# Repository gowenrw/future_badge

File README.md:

# future_badge

Future Badge Artifacts

This is a DEFCON Indie badge created for DC31.

This is where all the files for the Future Badge will be stored.

This includes code and art and cad and fab files.  All the things.

## File Structure

This is the file structure of this repository

* [/](/README.md) - YOU ARE HERE
* [/art/](./art/) - Artwork and other graphics created by this project
  * [/art/inspiration/](./art/inspiration/) - Art and graphics pulled from other sources used as inspiration for this project
  * [/art/fonts/](./art/fonts/) - Fonts used in art and graphics
* [/code/](./code/) - All project related Code / Firmware
* [/docs/](./docs/) - Documentation created by this project including web pages
* [/eda/](./eda/) - Electronic Design Automation files (i.e. KiCad)
  * [/eda/future_badge/](./eda/future_badge/) - KiCad 6.x project folder for the future_badge PCB
* [/reference_parts/](./reference_parts/) - Documentation pulled from other sources related to components
* [/README.md](/README.md) - This File
* [/LICENSE](/LICENSE) - Currently set to MIT

Note: the reference_parts directory is a link to a submodule repository.
To add it use the following cmd after cloning this:
```
git submodule add https://github.com/gowenrw/reference_parts reference_parts
```
This will make a link to the current commit of that repo.
To update it to a newer commit after its been added use this cmd:
```
git submodule update --init --recursive
```

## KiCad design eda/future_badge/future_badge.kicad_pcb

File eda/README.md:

# Electronic Design Automation

This is where all the Electronic Design Automation files for the PCB(s) will be stored.
The EDA used is KiCad 6.x unless otherwise specified.

## File Structure

This is the file structure of this repository

* [/](/README.md) - Home
* [/eda](/eda/) - YOU ARE HERE
  * /eda/<eda_project>/ - KiCad project folder for the named project PCB(s)
    * ./3d_models/ - This directory contains footprint 3d model files
    * ./gerber/ - This directory contains gerber formatted files for manufacturing
    * ./lib_fp/ - This directory contains footprint module directories
    * ./lib_sh/ - This directory contains schematic library files
    * ./snapshots/ - This directory contains prints of schematic / cad files and images of preview / final product

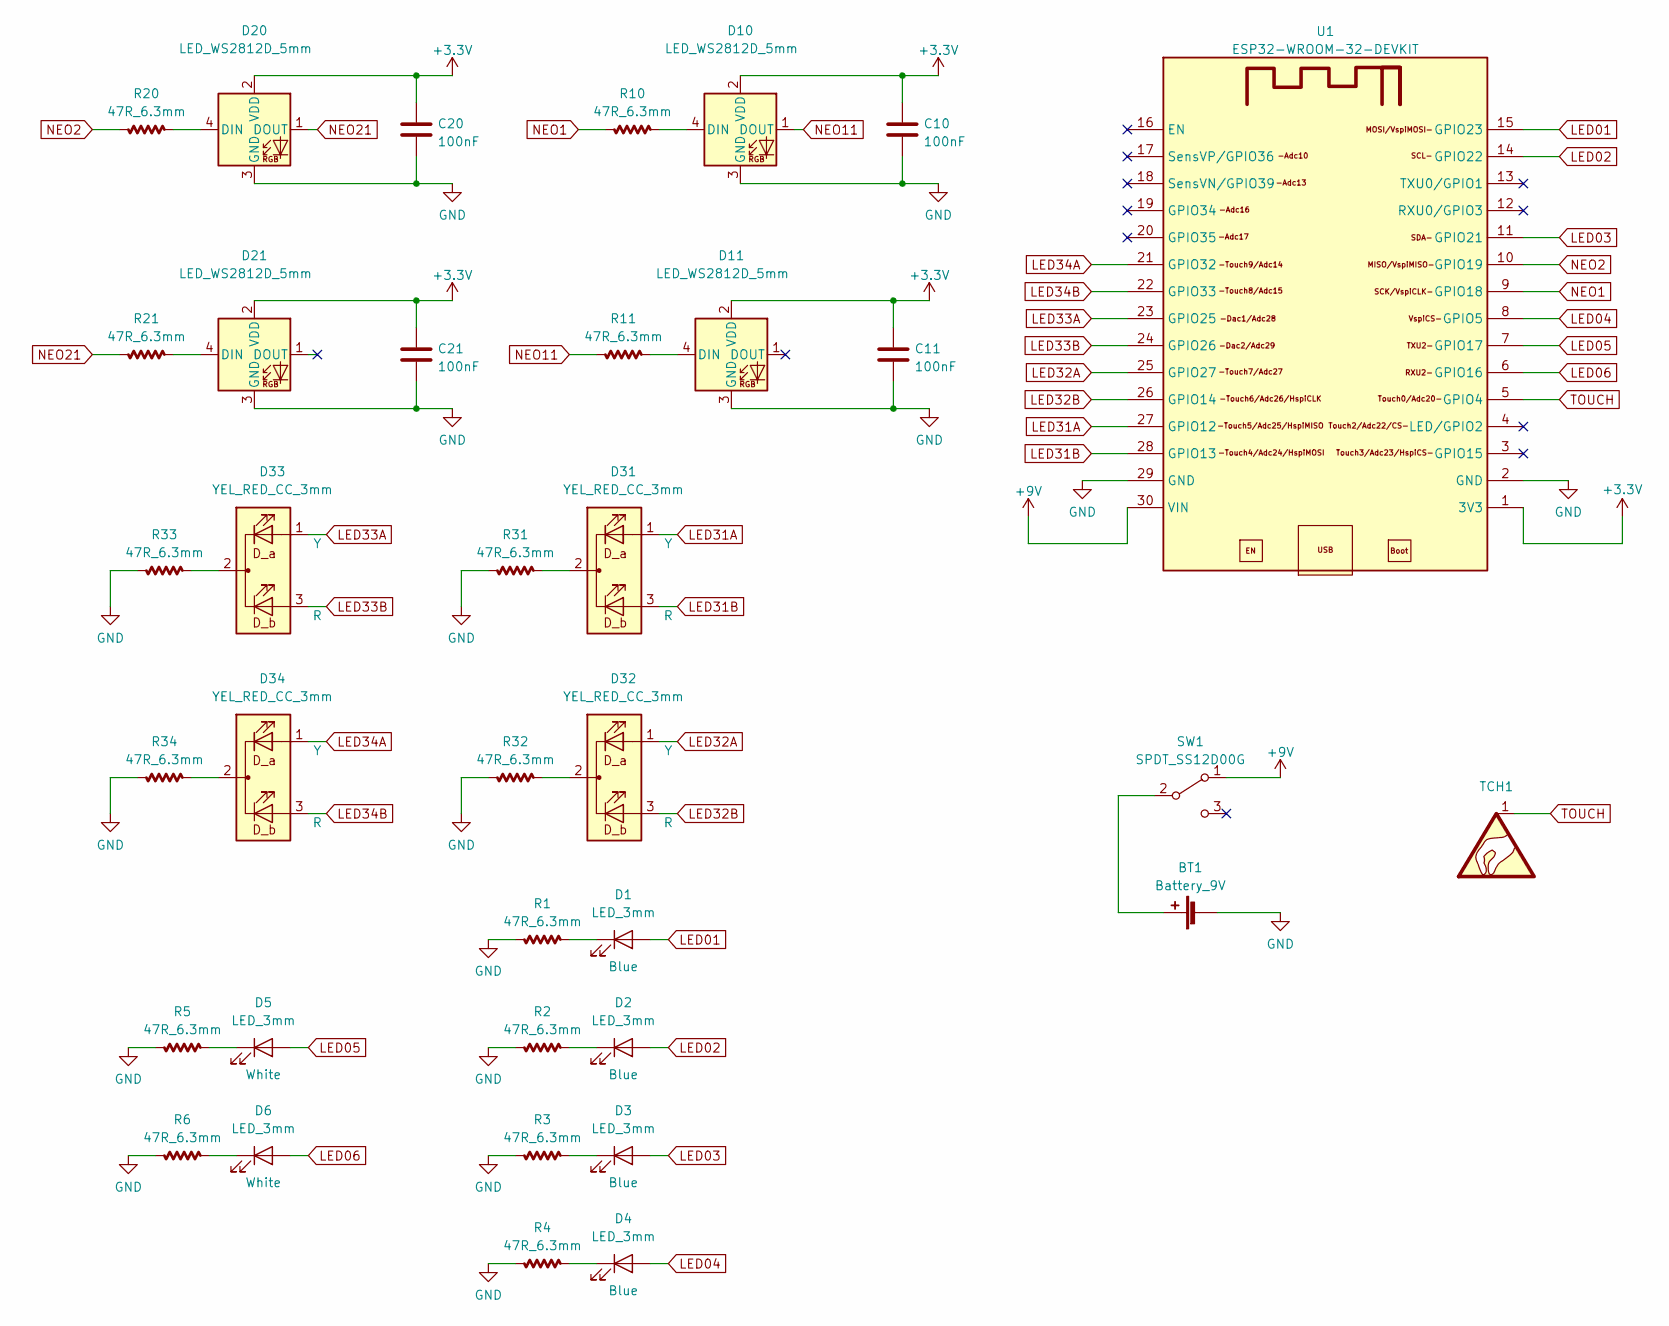
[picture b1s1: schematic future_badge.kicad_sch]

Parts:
BT1: Battery_9V; Battery_Lead_Wire_Connector
C10, C11, C20, C21: 100nF; C_Disc_D3.0mm_W2.0mm_P2.50mm
D1, D2, D3, D4, D5, D6: LED_3mm; LED_D3.0mm-2
D10, D11, D20, D21: LED_WS2812D_5mm; LED_D5.0mm-4_WS2812D_front_new
D31, D32, D33, D34: YEL_RED_CC_3mm; LED_D3.0mm-3-TwoColor
R1, R2, R3, R4, R5, R6, R10, R11, R20, R21, R31, R32, R33, R34: 47R_6.3mm; R_Axial_DIN0207_L6.3mm_D2.5mm_P7.62mm_Horizontal
SW1: SPDT_SS12D00G; SW_SPDT_Slide_SS12D00G-1P2T_3pin
TCH1: SYM_Touch_lg
U1: ESP32-WROOM-32-DEVKIT; ESP32_DEVKIT_V1

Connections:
+3.3V: C10.1, C11.1, C20.1, C21.1, D10.2 (VDD), D11.2 (VDD), D20.2 (VDD), D21.2 (VDD), U1.1 (3V3)
+9V: SW1.1 (A), U1.30 (VIN)
GND: BT1.2 (-), C10.2, C11.2, C20.2, C21.2, D10.3 (GND), D11.3 (GND), D20.3 (GND), D21.3 (GND), R1.1, R2.1, R3.1, R4.1, R5.1, R6.1, R31.1, R32.1, R33.1, R34.1, U1.2 (GND), U1.29 (GND)
LED01: D1.2 (A), U1.15 (GPIO23)
LED02: D2.2 (A), U1.14 (GPIO22)
LED03: D3.2 (A), U1.11 (GPIO21)
LED04: D4.2 (A), U1.8 (GPIO5)
LED05: D5.2 (A), U1.7 (GPIO17)
LED06: D6.2 (A), U1.6 (GPIO16)
LED31A: D31.1 (RA), U1.27 (GPIO12)
LED31B: D31.3 (BA), U1.28 (GPIO13)
LED32A: D32.1 (RA), U1.25 (GPIO27)
LED32B: D32.3 (BA), U1.26 (GPIO14)
LED33A: D33.1 (RA), U1.23 (GPIO25)
LED33B: D33.3 (BA), U1.24 (GPIO26)
LED34A: D34.1 (RA), U1.21 (GPIO32)
LED34B: D34.3 (BA), U1.22 (GPIO33)
NEO1: R10.1, U1.9 (GPIO18)
NEO2: R20.1, U1.10 (GPIO19)
NEO11: D10.1 (DOUT), R11.1
NEO21: D20.1 (DOUT), R21.1
unnamed: BT1.1 (+), SW1.2 (B)
unnamed: D1.1 (K), R1.2
unnamed: D2.1 (K), R2.2
unnamed: D3.1 (K), R3.2
unnamed: D4.1 (K), R4.2
unnamed: D5.1 (K), R5.2
unnamed: D6.1 (K), R6.2
unnamed: D10.4 (DIN), R10.2
unnamed: D11.4 (DIN), R11.2
unnamed: D20.4 (DIN), R20.2
unnamed: D21.4 (DIN), R21.2
unnamed: D31.2 (K), R31.2
unnamed: D32.2 (K), R32.2
unnamed: D33.2 (K), R33.2
unnamed: D34.2 (K), R34.2
TOUCH: TCH1.1, U1.5 (GPIO4)

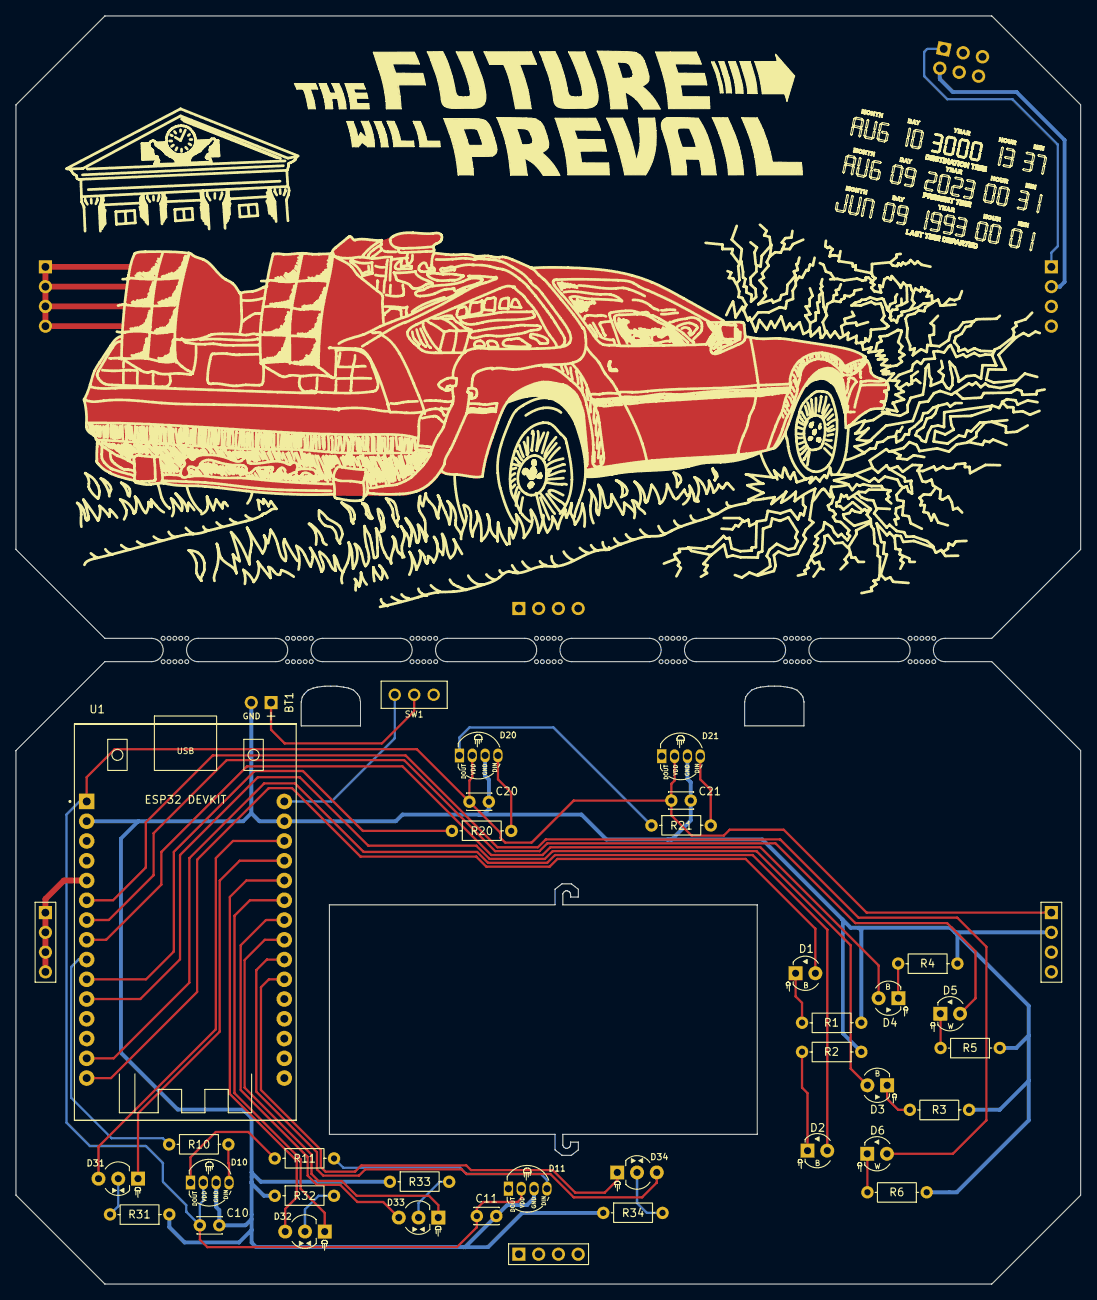
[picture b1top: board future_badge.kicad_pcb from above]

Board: 2 copper layers, 136.9 x 163.0 mm, 35 parts (0 on the bottom side), 36 nets.

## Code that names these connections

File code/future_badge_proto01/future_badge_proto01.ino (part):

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#include <WiFi.h>

// NeoPixel PIN VALUES
#define NEO01Pin 18   // 18 corresponds to GPIO18
#define NEO02Pin 19   // 18 corresponds to GPIO19

// Two color RY LED PIN VALUES
// The A pin is Yellow and the B pin is Red
#define LED31A 12  // 12 corresponds to GPIO12
#define LED31B 13  // 13 corresponds to GPIO13
#define LED32A 27
#define LED32B 14
#define LED33A 25
#define LED33B 26
#define LED34A 32
#define LED34B 33

// One color B/W LED PIN VALUES
#define LEDB01 23
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#define LEDW05 17
#define LEDW06 16

// Touch PIN VALUE
#define TouchPin 4  // 4 corresponds to GPIO4 - Touch0

// PWM Properties
const int freq = 1000;
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  ledcSetup(LED34Bpwm, freq, resolution);

  // attach the channel to the GPIO to be controlled
  ledcAttachPin(LED31A, LED31Apwm);
  ledcAttachPin(LED31B, LED31Bpwm);
  ledcAttachPin(LED32A, LED32Apwm);
  ledcAttachPin(LED32B, LED32Bpwm);
  ledcAttachPin(LED33A, LED33Apwm);
  ledcAttachPin(LED33B, LED33Bpwm);
  ledcAttachPin(LED34A, LED34Apwm);
  ledcAttachPin(LED34B, LED34Bpwm);

  //Normal LED output
  pinMode(LEDB01, OUTPUT);
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
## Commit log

2023-04-12 art push
2023-04-15 added file structure
2023-04-15 initial eda template added
2023-04-16 concept art
2023-04-17 updated art concept draft
2023-04-28 schematic start
2023-05-12 more stuff
2023-05-17 more test code and esp32 sch and fp and 3d
2023-05-19 updated schematic
2023-05-31 schematic and code and art updates
2023-06-03 art and footprint and pcb updates
2023-06-05 PCB layout
2023-06-06 prototype ordered
2023-06-14 proto code
2023-06-15 future proto code update
2023-06-17 prototype code and images
2023-06-17 make sure wifi is off for now
2023-06-19 pcb updates
2023-06-21 true edits for voltreg and cleanup
2023-06-23 incorporate updates from true
2023-06-26 pcb rev2 complete
2023-07-05 lantard art and code update
2023-07-05 doc website updates
2023-07-07 arduino cli configs and script
2023-07-07 code cleanup and cli scripts
2023-07-14 sticker and code updates
2023-07-21 doc updates
2023-07-21 web doc updates
2023-07-27 doc updates and labels
2023-07-29 preparing rev01 code
2023-07-31 Great Scott! We got the code working just in time.
2023-08-04 readme typo
2023-08-04 quality of life script
2023-08-05 update to qol script
2023-08-06 added walkthrough video link
2024-04-17 added ctf library source
